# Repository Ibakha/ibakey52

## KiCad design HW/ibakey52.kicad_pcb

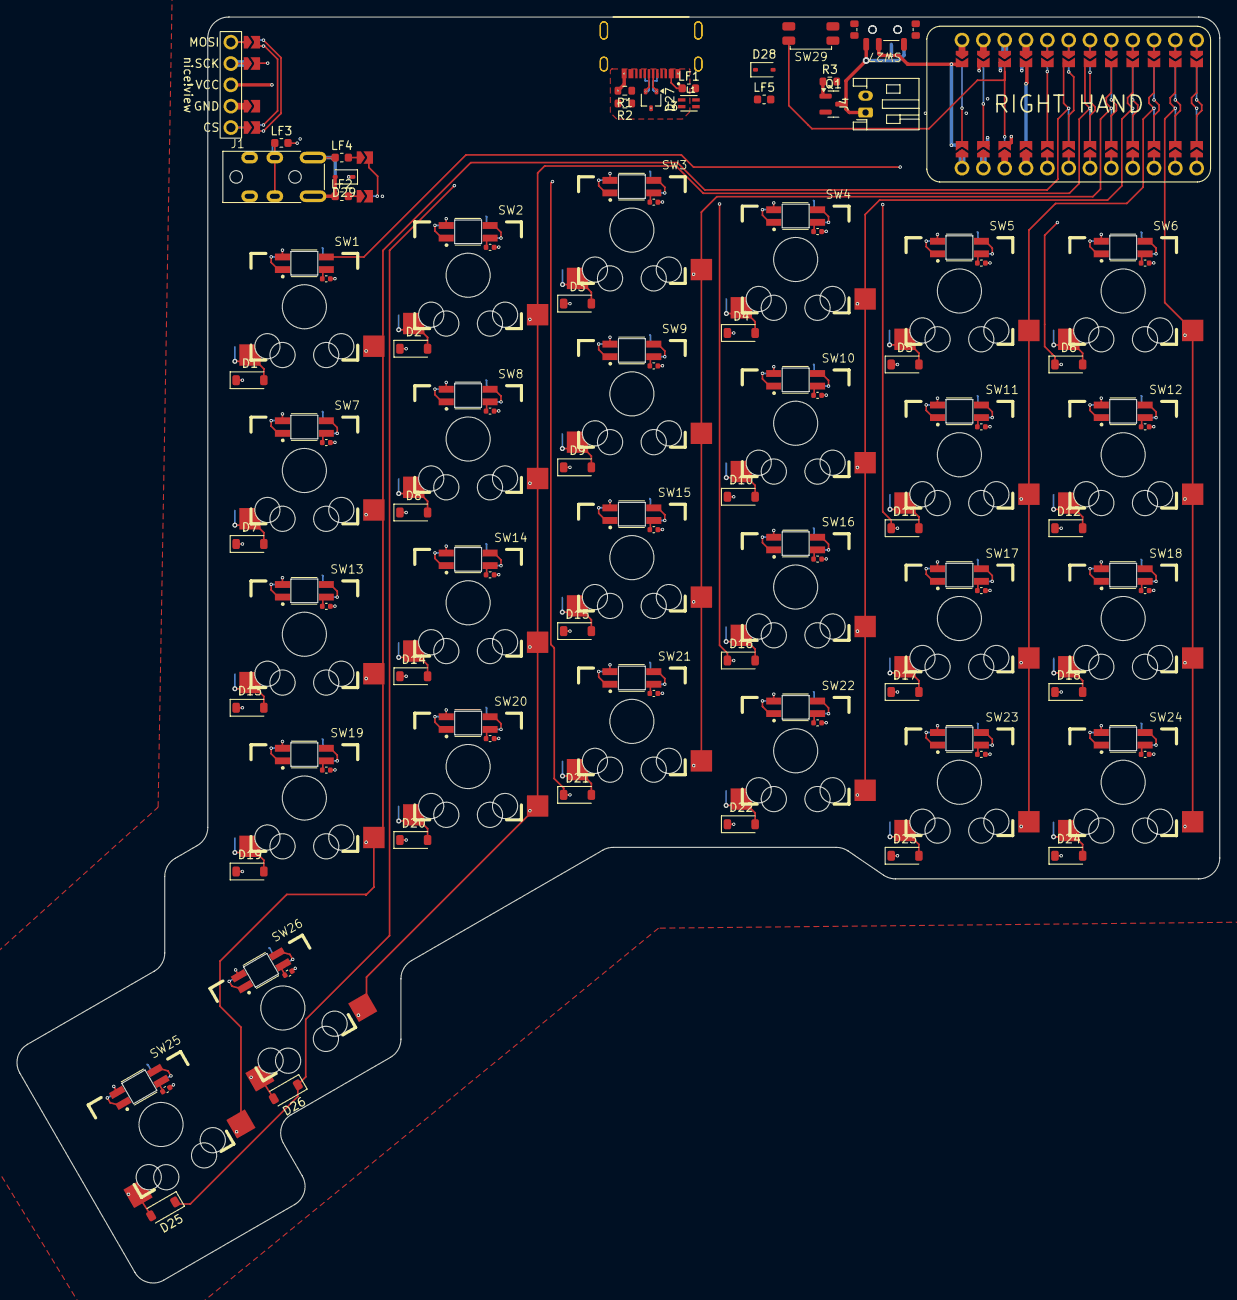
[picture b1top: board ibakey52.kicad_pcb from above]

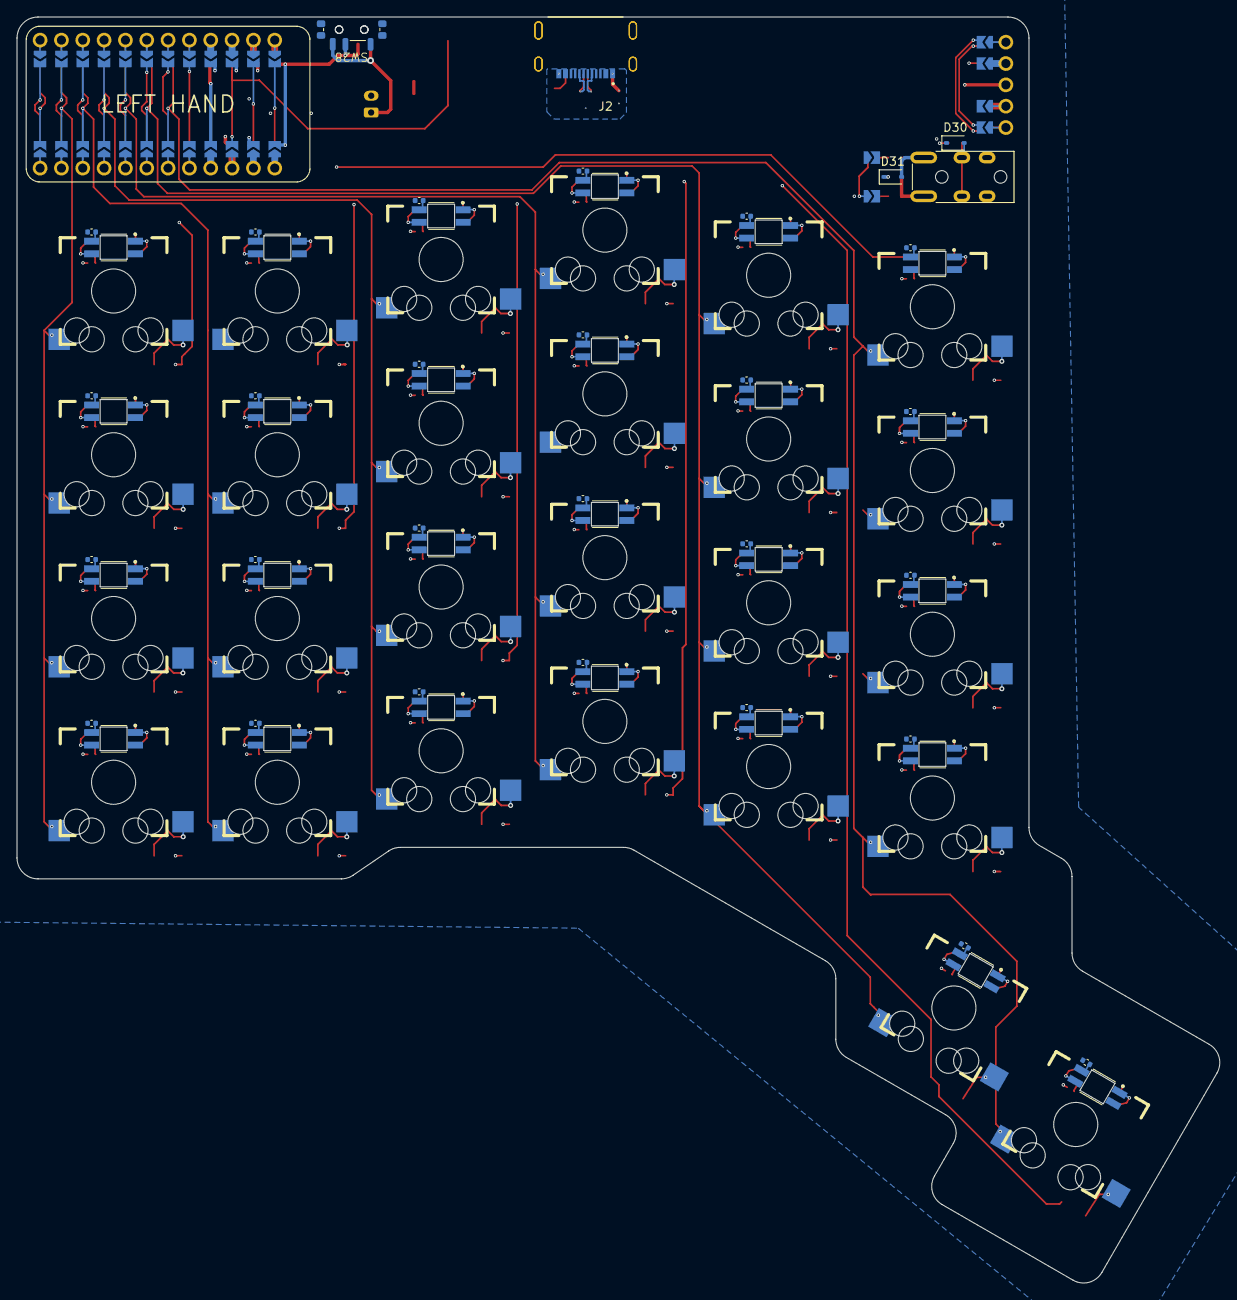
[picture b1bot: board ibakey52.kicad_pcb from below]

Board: 4 copper layers, 143.2 x 150.7 mm, 188 parts (60 on the bottom side), 116 nets.

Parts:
C1, C2, C3, C4, C5, C6, C7, C8, C9, C10, C11, C12, C13, C14, C15, C16, C17, C18, C19, C20, C21, C22, C23, C24, C25, C26, C27, C28, C29, C30, C31, C32, C33, C34, C35, C36, C37, C38, C39, C40, C41, C42, C43, C44, C45, C46, C47, C48, C49, C50, C51, C52: c=100n; C_0402_1005Metric
D1, D2, D3, D4, D5, D6, D7, D8, D9, D10, D11, D12, D13, D14, D15, D16, D17, D18, D19, D20, D21, D22, D23, D24, D25, D26: 1N4148W; D_SOD-123
D27: D1213A-02WLQ-7; SOT-323_SC-70
D28, D29, D30, D31: DESD5V0U1BA-7; D_SOD-323
Display1: nice!view; nice_view
J1: AudioJack4; PJ-320A
J2, J3: USB_C_Receptacle_USB2.0_16P; GCT_USB4520-03-0-A_REVA
J4: JST_PH_S2B-PH-K_1x02_P2.00mm_Horizontal
JP2, JP3, JP4, JP5, JP6, JP7, JP8, JP9, JP10, JP11, JP12, JP13, JP14, JP15, JP16, JP17, JP18, JP19, JP20, JP21, JP22, JP23, JP24, JP25, JP28, JP29, JP30, JP31, JP32, JP33, JP34, JP35, JP36, JP37, JP38, JP39, JP40, JP41, JP42, JP43, JP44, JP45, JP46, JP47, JP48, JP49, JP50, JP51, JP53, JP54, JP55, JP56, JP57, JP58, JP59, JP60, JP61, JP62, JP63, JP64: SolderJumper_2_Open; SJMP1.3mm
L1: DLW21HN900SQ2L; FIL_DLW21HN900SQ2L
LF1, LF2, LF3, LF4, LF5: MPZ1608S601ATA00; L_0603_1608Metric
Q1: Si2371EDS; SOT-23
R1, R2, R3: r=2.2k; R_0603_1608Metric
SW1, SW2, SW3, SW4, SW5, SW6, SW7, SW8, SW9, SW10, SW11, SW12, SW13, SW14, SW15, SW16, SW17, SW18, SW19, SW20, SW21, SW22, SW23, SW24, SW25, SW26: GATERON-MX-HOTSWAP-RGB; SWITCH-GATERON-LOW-HOT
SW27, SW28: SSSS811101
SW29: SW_Push; EVQ-PUL02K
U1: Nice!Nano

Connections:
+3.3V: Display1.3 (VCC), JP31.2 (B), JP48.2 (B)
/COL0: JP33.2 (B), JP46.2 (B), SW1.6, SW7.6, SW13.6, SW19.6, SW25.6
/COL1: JP34.2 (B), JP45.2 (B), SW2.6, SW8.6, SW14.6, SW20.6, SW26.6
/COL2: JP35.2 (B), JP44.2 (B), SW3.6, SW9.6, SW15.6, SW21.6
/COL3: JP36.2 (B), JP43.2 (B), SW4.6, SW10.6, SW16.6, SW22.6
/COL4: JP37.2 (B), JP42.2 (B), SW5.6, SW11.6, SW17.6, SW23.6
/COL5: JP38.2 (B), JP41.2 (B), SW6.6, SW12.6, SW18.6, SW24.6
/CS: JP8.2 (B), JP19.2 (B), JP59.2 (B), JP60.2 (B)
/LED_D: JP9.2 (B), JP18.2 (B), SW1.3 (DIN)
/MOSI: JP7.2 (B), JP20.2 (B), JP53.2 (B), JP54.2 (B)
/PIN2: JP2.1 (A), JP51.1 (A), U1.1 (D1/P0.06)
/PIN3: JP3.1 (A), JP50.1 (A), U1.2 (D0/P0.08)
/PIN4: JP4.1 (A), JP49.1 (A), U1.3 (GND)
/PIN5: JP5.1 (A), JP48.1 (A), U1.4 (GND)
/PIN6: JP6.1 (A), JP47.1 (A), U1.5 (D2/P0.17)
/PIN7: JP7.1 (A), JP46.1 (A), U1.6 (D3/P0.20)
/PIN8: JP8.1 (A), JP45.1 (A), U1.7 (D4/P0.22)
/PIN9: JP9.1 (A), JP44.1 (A), U1.8 (D5/P0.24)
/PIN10: JP10.1 (A), JP43.1 (A), U1.9 (D6/P1.00)
/PIN11: JP11.1 (A), JP42.1 (A), U1.10 (D7/P0.11)
/PIN12: JP12.1 (A), JP41.1 (A), U1.11 (D8/P1.04)
/PIN13: JP13.1 (A), JP40.1 (A), U1.12 (D9/P1.06)
/PIN14: JP14.1 (A), JP39.1 (A), U1.13 (D10/P0.09)
/PIN15: JP15.1 (A), JP38.1 (A), U1.14 (D16/P0.10)
/PIN16: JP16.1 (A), JP37.1 (A), U1.15 (D14/P1.11)
/PIN17: JP17.1 (A), JP36.1 (A), U1.16 (D15/P1.13)
/PIN18: JP18.1 (A), JP35.1 (A), U1.17 (D18/P1.15)
/PIN19: JP19.1 (A), JP34.1 (A), U1.18 (D19/P0.02)
/PIN20: JP20.1 (A), JP33.1 (A), U1.19 (D20/P0.29)
/PIN21: JP21.1 (A), JP32.1 (A), U1.20 (D21/P0.31)
/PIN22: JP22.1 (A), JP31.1 (A), U1.21 (3.3V)
/PIN23: JP23.1 (A), JP30.1 (A), U1.22 (~RST)
/PIN24: JP24.1 (A), JP29.1 (A), U1.23 (GND)
/PIN25: JP25.1 (A), JP28.1 (A), U1.24 (VBATT)
/ROW0: D1.1 (K), D2.1 (K), D3.1 (K), D4.1 (K), D5.1 (K), D6.1 (K), JP10.2 (B), JP17.2 (B)
/ROW1: D7.1 (K), D8.1 (K), D9.1 (K), D10.1 (K), D11.1 (K), D12.1 (K), JP11.2 (B), JP16.2 (B)
/ROW2: D13.1 (K), D14.1 (K), D15.1 (K), D16.1 (K), D17.1 (K), D18.1 (K), JP12.2 (B), JP15.2 (B)
/ROW3: D19.1 (K), D20.1 (K), D21.1 (K), D22.1 (K), D23.1 (K), D24.1 (K), JP13.2 (B), JP14.2 (B)
/ROW4: D25.1 (K), D26.1 (K), JP39.2 (B), JP40.2 (B)
/SCK: JP6.2 (B), JP21.2 (B), JP55.2 (B), JP56.2 (B)
/SCL: JP3.2 (B), JP24.2 (B), LF3.2
/SDA: JP2.2 (B), JP25.2 (B), JP63.2 (B), JP64.1 (A)
/USB_D+: D27.1 (A1), J2.A6 (D+), J2.B6 (D+), L1.4
/USB_D-: D27.2 (A2), J2.A7 (D-), J2.B7 (D-), L1.1
/~RST: JP30.2 (B), JP49.2 (B), SW29.2
GND: C1.1, C2.1, C3.1, C4.1, C5.1, C6.1, C7.1, C8.1, C9.1, C10.1, C11.1, C12.1, C13.1, C14.1, C15.1, C16.1, C17.1, C18.1, C19.1, C20.1, C21.1, C22.1, C23.1, C24.1, C25.1, C26.1, C27.1, C28.1, C29.1, C30.1, C31.1, C32.1, C33.1, C34.1, C35.1, C36.1, C37.1, C38.1, C39.1, C40.1, C41.1, C42.1, C43.1, C44.1, C45.1, C46.1, C47.1, C48.1, C49.1, C50.1, C51.1, C52.1, D29.1 (A1), D30.1 (A1), D31.1 (A1), J1.R2, J4.2, JP4.2 (B), JP5.2 (B), JP22.2 (B), JP23.2 (B), JP29.2 (B), JP50.2 (B), JP57.2 (B), JP58.2 (B), LF5.2, SW1.2 (VSS), SW2.2 (VSS), SW3.2 (VSS), SW4.2 (VSS), SW5.2 (VSS), SW6.2 (VSS), SW7.2 (VSS), SW8.2 (VSS), SW9.2 (VSS), SW10.2 (VSS), SW11.2 (VSS), SW12.2 (VSS), SW13.2 (VSS), SW14.2 (VSS), SW15.2 (VSS), SW16.2 (VSS), SW17.2 (VSS), SW18.2 (VSS), SW19.2 (VSS), SW20.2 (VSS), SW21.2 (VSS), SW22.2 (VSS), SW23.2 (VSS), SW24.2 (VSS), SW25.2 (VSS), SW26.2 (VSS), SW27.4 (GND), SW28.4 (GND), SW29.1
unnamed: D1.2 (A), SW1.5
unnamed: D2.2 (A), SW2.5
unnamed: D3.2 (A), SW3.5
unnamed: D4.2 (A), SW4.5
unnamed: D5.2 (A), SW5.5
unnamed: D6.2 (A), SW6.5
unnamed: D7.2 (A), SW7.5
unnamed: D8.2 (A), SW8.5
unnamed: D9.2 (A), SW9.5
unnamed: D10.2 (A), SW10.5
unnamed: D11.2 (A), SW11.5
unnamed: D12.2 (A), SW12.5
unnamed: D13.2 (A), SW13.5
unnamed: D14.2 (A), SW14.5
unnamed: D15.2 (A), SW15.5
unnamed: D16.2 (A), SW16.5
unnamed: D17.2 (A), SW17.5
unnamed: D18.2 (A), SW18.5
unnamed: D19.2 (A), SW19.5
unnamed: D20.2 (A), SW20.5
unnamed: D21.2 (A), SW21.5
unnamed: D22.2 (A), SW22.5
unnamed: D23.2 (A), SW23.5
unnamed: D24.2 (A), SW24.5
unnamed: D25.2 (A), SW25.5
unnamed: D26.2 (A), SW26.5
unnamed: D27.3 (common), D28.1 (A1), J2.A1 (GND), J2.B1 (GND), LF5.1, R1.2, R2.2
unnamed: D28.2 (A2), J2.A4 (VBUS), J2.B4 (VBUS), LF1.1
unnamed: D29.2 (A2), J1.S, LF2.1
unnamed: D30.2 (A2), J1.R1, LF3.1
unnamed: D31.2 (A2), J1.T, LF4.1
unnamed: Display1.5 (CS), JP54.1 (A), JP59.1 (A)
unnamed: Display1.4 (GND), JP56.1 (A), JP57.1 (A)
unnamed: Display1.1 (MOSI), JP53.1 (A), JP60.1 (A)
unnamed: Display1.2 (SCK), JP55.1 (A), JP58.1 (A)
unnamed: J2.A5 (CC1), R2.1
unnamed: J2.B5 (CC2), R1.1
unnamed: J3.A1 (GND), J3.B1 (GND)
unnamed: J3.A4 (VBUS), J3.B4 (VBUS)
unnamed: JP61.1 (A), JP64.2 (B), LF2.2
unnamed: JP62.2 (B), JP63.1 (A), LF4.2
unnamed: J4.1, Q1.3 (D), SW27.1 (A), SW28.1 (A)
unnamed: SW1.1 (DOUT), SW2.3 (DIN)
unnamed: SW2.1 (DOUT), SW3.3 (DIN)
unnamed: SW3.1 (DOUT), SW4.3 (DIN)
unnamed: SW4.1 (DOUT), SW5.3 (DIN)
unnamed: SW5.1 (DOUT), SW6.3 (DIN)
unnamed: SW6.1 (DOUT), SW7.3 (DIN)
unnamed: SW7.1 (DOUT), SW8.3 (DIN)
unnamed: SW8.1 (DOUT), SW9.3 (DIN)
unnamed: SW9.1 (DOUT), SW10.3 (DIN)
unnamed: SW10.1 (DOUT), SW11.3 (DIN)
unnamed: SW11.1 (DOUT), SW12.3 (DIN)
unnamed: SW12.1 (DOUT), SW13.3 (DIN)
unnamed: SW13.1 (DOUT), SW14.3 (DIN)
unnamed: SW14.1 (DOUT), SW15.3 (DIN)
unnamed: SW15.1 (DOUT), SW16.3 (DIN)
unnamed: SW16.1 (DOUT), SW17.3 (DIN)
unnamed: SW17.1 (DOUT), SW18.3 (DIN)
unnamed: SW18.1 (DOUT), SW19.3 (DIN)
unnamed: SW19.1 (DOUT), SW20.3 (DIN)
unnamed: SW20.1 (DOUT), SW21.3 (DIN)
unnamed: SW21.1 (DOUT), SW22.3 (DIN)
unnamed: SW22.1 (DOUT), SW23.3 (DIN)
unnamed: SW23.1 (DOUT), SW24.3 (DIN)
unnamed: SW24.1 (DOUT), SW25.3 (DIN)
unnamed: SW25.1 (DOUT), SW26.3 (DIN)
VBATT: JP28.2 (B), JP51.2 (B), SW27.2 (B), SW28.2 (B)
VBUS: JP61.2 (B), JP62.1 (A), LF1.2, R3.2
VDD: C1.2, C2.2, C3.2, C4.2, C5.2, C6.2, C7.2, C8.2, C9.2, C10.2, C11.2, C12.2, C13.2, C14.2, C15.2, C16.2, C17.2, C18.2, C19.2, C20.2, C21.2, C22.2, C23.2, C24.2, C25.2, C26.2, C27.2, C28.2, C29.2, C30.2, C31.2, C32.2, C33.2, C34.2, C35.2, C36.2, C37.2, C38.2, C39.2, C40.2, C41.2, C42.2, C43.2, C44.2, C45.2, C46.2, C47.2, C48.2, C49.2, C50.2, C51.2, C52.2, Q1.2 (S), SW1.4 (VDD), SW2.4 (VDD), SW3.4 (VDD), SW4.4 (VDD), SW5.4 (VDD), SW6.4 (VDD), SW7.4 (VDD), SW8.4 (VDD), SW9.4 (VDD), SW10.4 (VDD), SW11.4 (VDD), SW12.4 (VDD), SW13.4 (VDD), SW14.4 (VDD), SW15.4 (VDD), SW16.4 (VDD), SW17.4 (VDD), SW18.4 (VDD), SW19.4 (VDD), SW20.4 (VDD), SW21.4 (VDD), SW22.4 (VDD), SW23.4 (VDD), SW24.4 (VDD), SW25.4 (VDD), SW26.4 (VDD)

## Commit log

2024-02-28 adding gitignore
2024-02-28 switch placements
2024-03-02 finishing main placement & board shape
2024-03-02 Renaming project
2024-03-02 removing.lck
2024-03-08 matrix routed
2024-03-09 updating gitignore
2024-03-09 correcting switch footprint & updating LED routing
2024-03-13 ibakey52v1.0
